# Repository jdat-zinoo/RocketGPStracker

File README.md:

# RocketGPStracker

Atmega328P (arduino based) tiny GPS tracker for model rockets.

Additional package:
https://github.com/SpenceKonde/ATTinyCore
JSon board URL: http://drazzy.com/package_drazzy.com_index.json

TinyWireM lib:
https://github.com/SpenceKonde/TinyWireM

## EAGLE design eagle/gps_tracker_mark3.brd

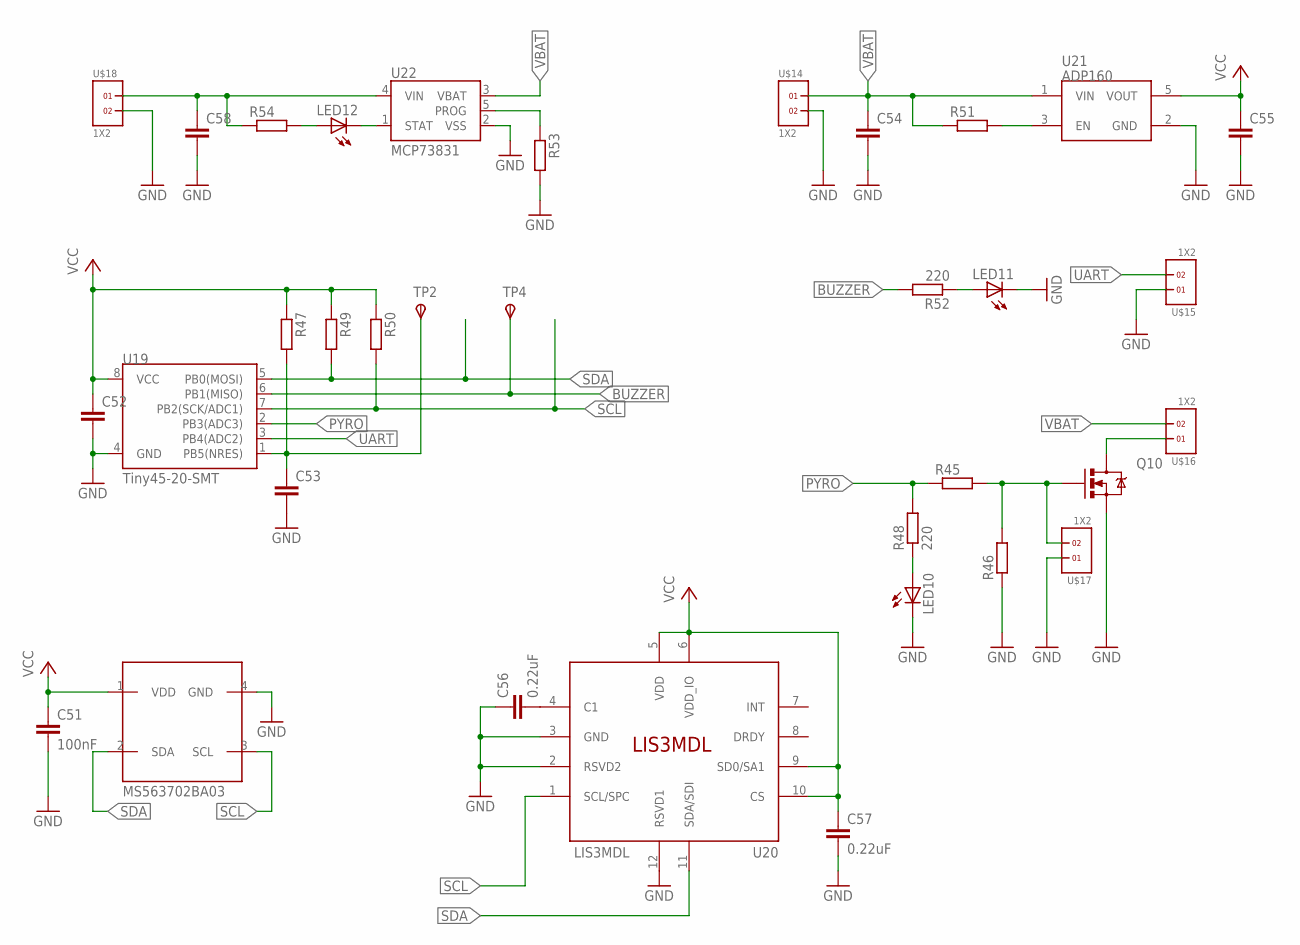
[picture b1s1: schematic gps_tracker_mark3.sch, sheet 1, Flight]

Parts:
C51: 100nF; C0603
C52: C-EUC1206; C1206
C53, C54, C55, C58: C-EUC0603; C0603
C56: 0.22uF; C0603K
C57: 0.22uF; C0603
IC2: MS563702BA03; MS5637
LED10, LED11: LEDCHIPLED_0805; CHIPLED_0805
LED12: LEDCHIPLED_0603; CHIPLED_0603
Q10: MOSFET-NCHANNELBSS123LT1G; SOT23-3
R45, R46, R47, R49, R50, R51, R53, R54: R-EU_R0603; R0603
R48, R52: 220; R0603
TP2, TP4: TPSB1,27; B1,27
U19: Tiny45-20-SMT; SO08-EIAJ
U20: LIS3MDL; VFLGA-12
U21: ADP160; SOT23-5; FARNELL 2510377
U22: MCP73831; SOT23-5; FARNELL 1834892
U$14, U$15, U$16, U$17, U$18: 1X2

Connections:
BUZZER: R52.2, TP4.TP, U19.6 (PB1(MISO))
GND: C51.2, C52.2, C53.2, C54.2, C55.2, C56.1, C57.2, C58.2, IC2.4 (GND), LED10.C, LED11.C, Q10.2 (S), R46.1, R53.2, U19.4 (GND), U20.2 (RSVD2), U20.3 (GND), U20.12 (RSVD1), U21.2 (GND), U22.2 (VSS), U$14.2, U$15.1, U$17.1, U$18.2
unnamed: C53.1, R47.2, TP2.TP, U19.1 (PB5(NRES))
unnamed: Q10.1 (G), R45.2, R46.2, U$17.2
unnamed: LED10.A, R48.1
unnamed: C56.2, U20.4 (C1)
unnamed: R51.2, U21.3 (EN)
unnamed: LED11.A, R52.1
unnamed: Q10.3 (D), U$16.1
unnamed: R53.1, U22.5 (PROG)
unnamed: LED12.C, U22.1 (STAT)
unnamed: LED12.A, R54.2
unnamed: C58.1, R54.1, U22.4 (VIN), U$18.1
PYRO: R45.1, R48.2, U19.2 (PB3(ADC3))
SCL: IC2.3 (SCL), R50.2, U19.7 (PB2(SCK/ADC1)), U20.1 (SCL/SPC)
SDA: IC2.2 (SDA), R49.2, U19.5 (PB0(MOSI)), U20.11 (SDA/SDI)
UART: U19.3 (PB4(ADC2)), U$15.2
VBAT: C54.1, R51.1, U21.1 (VIN), U22.3 (VBAT), U$14.1, U$16.2
VCC: C51.1, C52.1, C55.1, C57.1, IC2.1 (VDD), R47.1, R49.1, R50.1, U19.8 (VCC), U20.5 (VDD), U20.6 (VDD_IO), U20.9 (SD0/SA1), U20.10 (CS), U21.5 (VOUT)

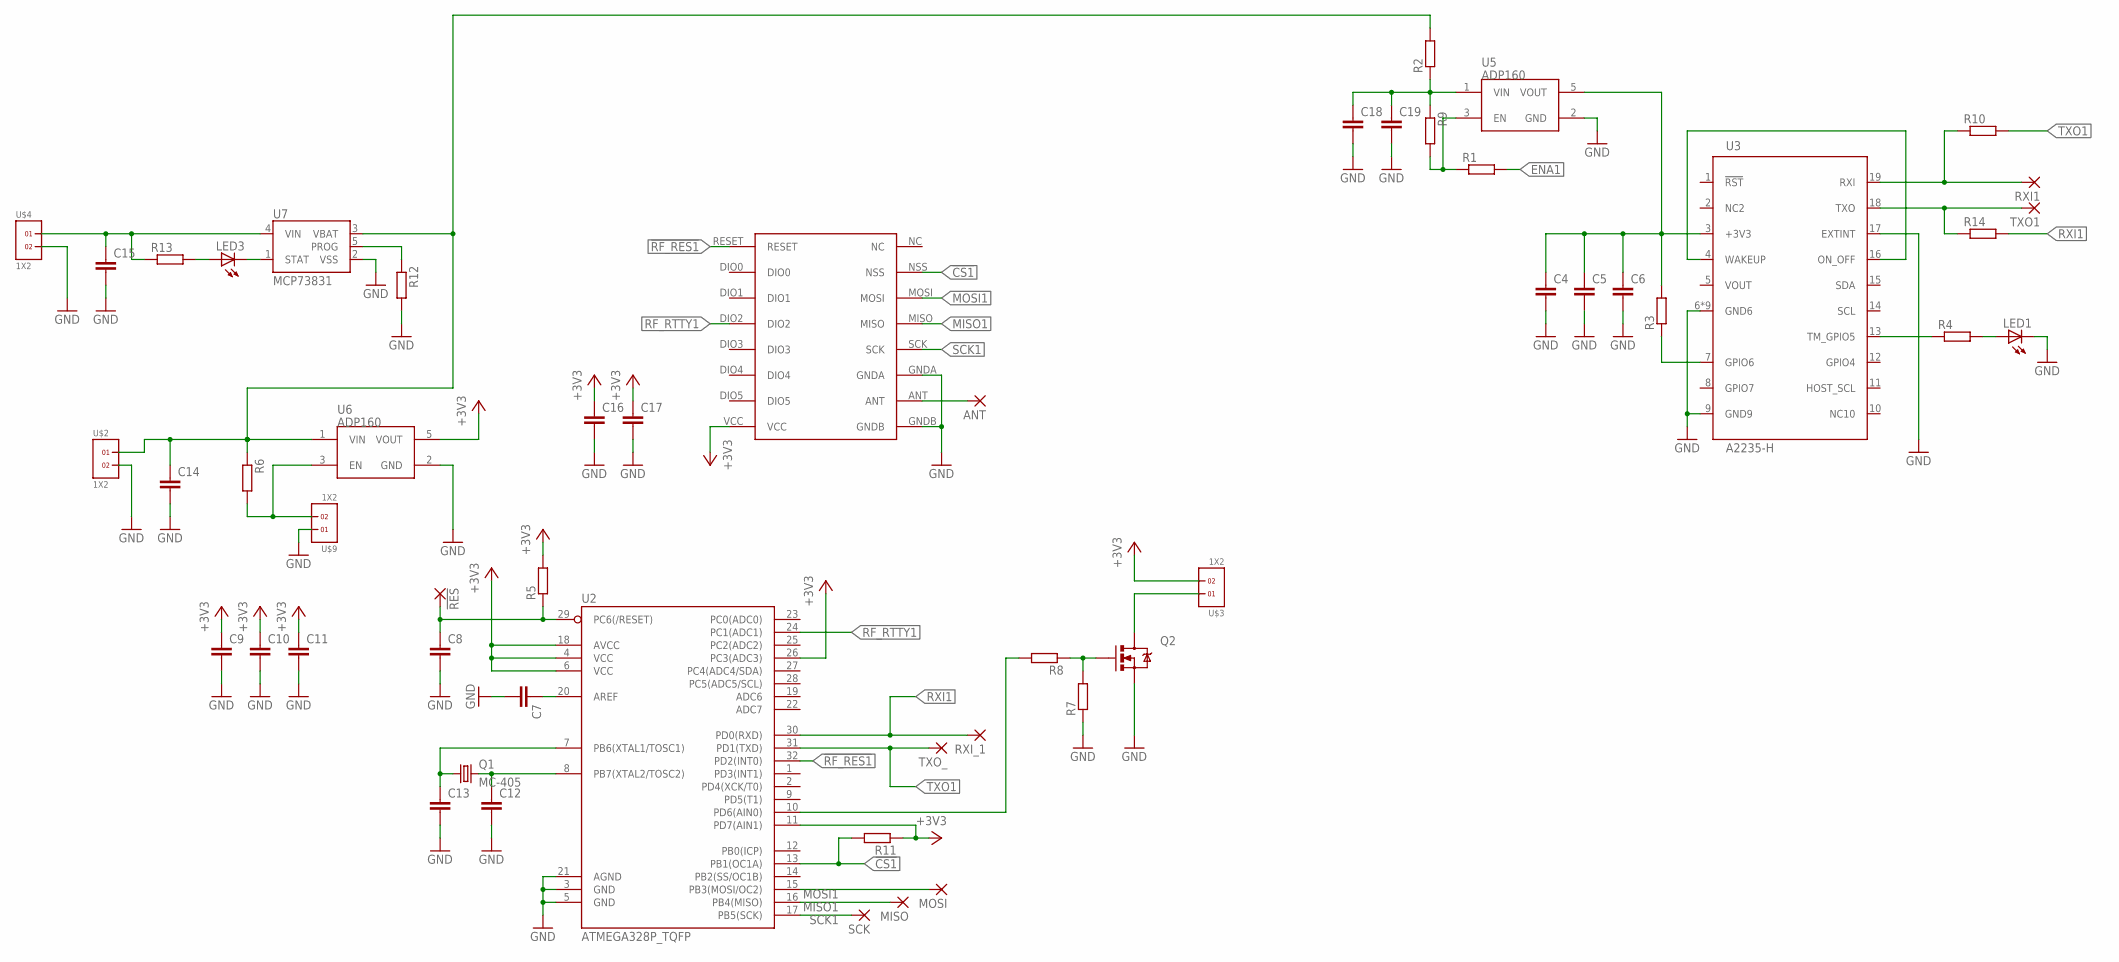
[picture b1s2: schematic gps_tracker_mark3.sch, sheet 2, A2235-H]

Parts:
!RES: SMD2; SMD1,27-2,54
ANT: SMD2; SMD1,27-2,54
C4, C5, C6, C7, C8, C9, C10, C11, C12, C13, C14, C15, C16, C17, C18, C19: C-EUC0603; C0603
LED1, LED3: LEDCHIPLED_0603; CHIPLED_0603
MISO: SMD2; SMD1,27-2,54
MOSI: SMD2; SMD1,27-2,54
Q1: MC-405; FARNELL 2508596
Q2: MOSFET-NCHANNELAO3404A; SOT23-3
R1, R2, R3, R4, R5, R6, R7, R8, R9, R10, R11, R12, R13, R14: R-EU_R0603; R0603
RXI1: SMD2; SMD1,27-2,54
RXI_1: SMD2; SMD1,27-2,54
SCK: SMD2; SMD1,27-2,54
TXO1: SMD2; SMD1,27-2,54
TXO_: SMD2; SMD1,27-2,54
U2: ATMEGA328P_TQFP; TQFP32-08
U3: A2235-H
U5, U6: ADP160; SOT23-5; FARNELL 2510377
U7: MCP73831; SOT23-5; FARNELL 1834892
U$1: RFM69HW; RFM
U$2, U$3, U$4, U$9: 1X2

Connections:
!CS1: R11.2, U2.13 (PB1(OC1A)), U$1.NSS
!RF_RES1: U2.32 (PD2(INT0)), U$1.RESET
+3V3_1: C9.1, C10.1, C11.1, C16.1, C17.1, R5.2, R11.1, U2.4 (VCC), U2.6 (VCC), U2.11 (PD7(AIN1)), U2.18 (AVCC), U2.26 (PC3(ADC3)), U6.5 (VOUT), U$1.VCC, U$3.2
+BAT1: C14.1, R2.2, R6.1, U6.1 (VIN), U7.3 (VBAT), U$2.1
ENA1: R1.2, R6.2, U6.3 (EN), U$9.2
GND1: C4.2, C5.2, C6.2, C7.2, C8.2, C9.2, C10.2, C11.2, C12.2, C13.2, C14.2, C15.2, C16.2, C17.2, C18.2, C19.2, LED1.C, Q2.2 (S), R7.1, R12.2, U2.3 (GND), U2.5 (GND), U2.21 (AGND), U3.6 (GND6), U3.9 (GND9), U3.17 (EXTINT), U3.101 (GND6), U3.102 (GND6), U3.103 (GND6), U3.104 (GND6), U3.105 (GND6), U3.106 (GND6), U3.107 (GND6), U3.108 (GND6), U5.2 (GND), U6.2 (GND), U7.2 (VSS), U$1.GNDA, U$1.GNDB, U$2.2, U$4.2, U$9.1
MISO1: MISO.1, U2.16 (PB4(MISO)), U$1.MISO
MOSI1: MOSI.1, U2.15 (PB3(MOSI/OC2)), U$1.MOSI
unnamed: R1.1, R9.2, U5.3 (EN)
unnamed: C18.1, C19.1, R2.1, R9.1, U5.1 (VIN)
unnamed: R3.1, U3.7 (GPIO6)
unnamed: LED1.A, R4.2
unnamed: R4.1, U3.13 (TM_GPIO5)
unnamed: U3.4 (WAKEUP), U3.16 (ON_OFF)
unnamed: R12.1, U7.5 (PROG)
unnamed: C7.1, U2.20 (AREF)
unnamed: !RES.1, C8.1, R5.1, U2.29 (PC6(/RESET))
unnamed: ANT.1, U$1.ANT
unnamed: C12.1, Q1.2, U2.8 (PB7(XTAL2/TOSC2))
unnamed: C13.1, Q1.1, U2.7 (PB6(XTAL1/TOSC1))
unnamed: LED3.C, U7.1 (STAT)
unnamed: Q2.1 (G), R7.2, R8.1
unnamed: R8.2, U2.10 (PD6(AIN0))
unnamed: Q2.3 (D), U$3.1
unnamed: LED3.A, R13.2
unnamed: C15.1, R13.1, U7.4 (VIN), U$4.1
unnamed: C4.1, C5.1, C6.1, R3.2, U3.3 (+3V3), U5.5 (VOUT)
RF_RTTY1: U2.24 (PC1(ADC1)), U$1.DIO2
RXI1: R14.2, RXI_1.1, U2.30 (PD0(RXD))
RXI_G1: R10.1, RXI1.1, U3.19 (RXI)
SCK1: SCK.1, U2.17 (PB5(SCK)), U$1.SCK
TXO1: R10.2, TXO_.1, U2.31 (PD1(TXD))
TXO_G1: R14.1, TXO1.1, U3.18 (TXO)
VOUT: U3.5 (VOUT)

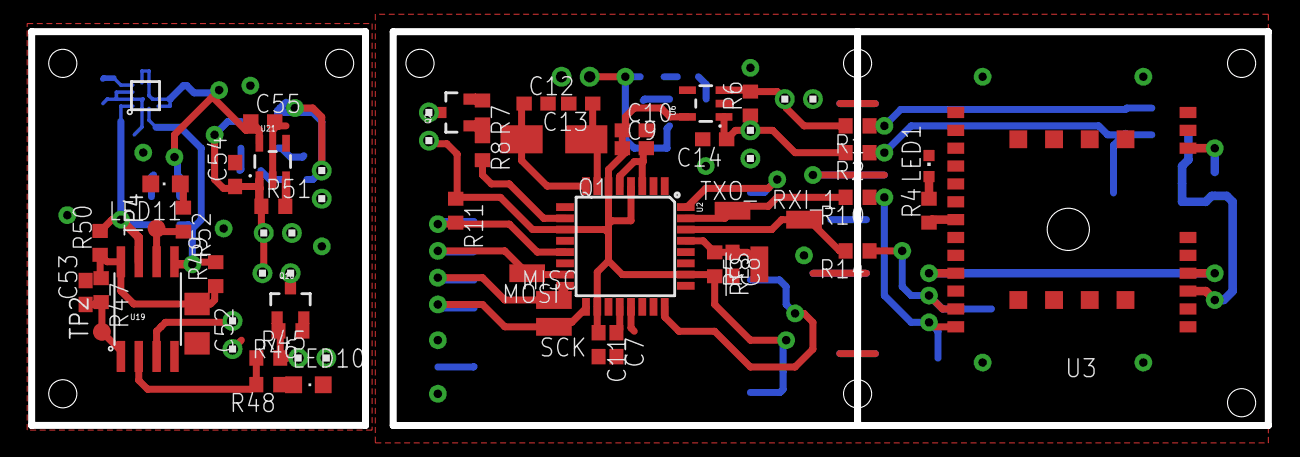
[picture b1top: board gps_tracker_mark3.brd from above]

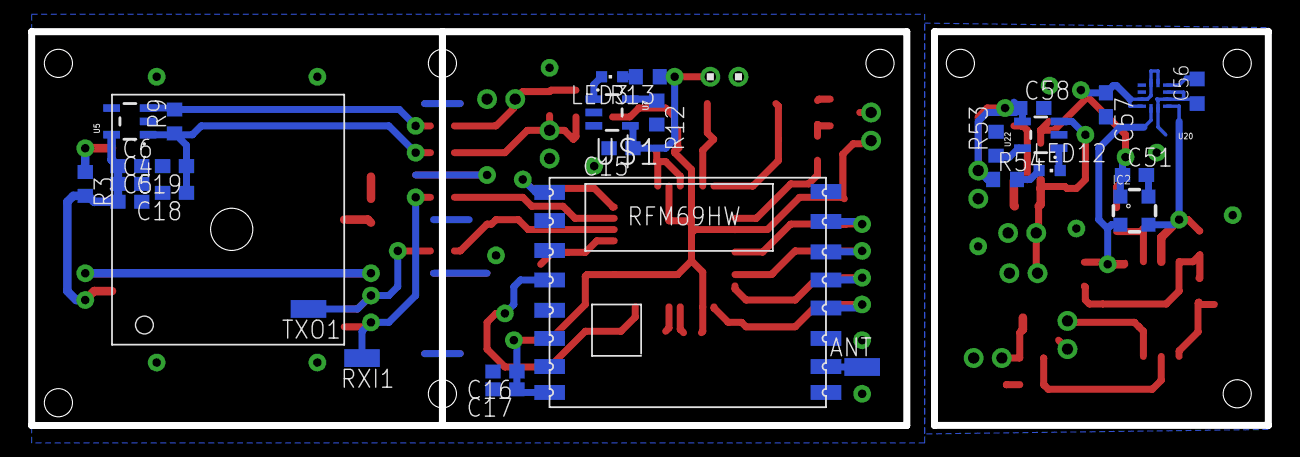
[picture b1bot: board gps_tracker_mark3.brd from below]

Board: 2 copper layers, 87.9 x 28.0 mm, 87 parts (30 on the bottom side), 52 nets.

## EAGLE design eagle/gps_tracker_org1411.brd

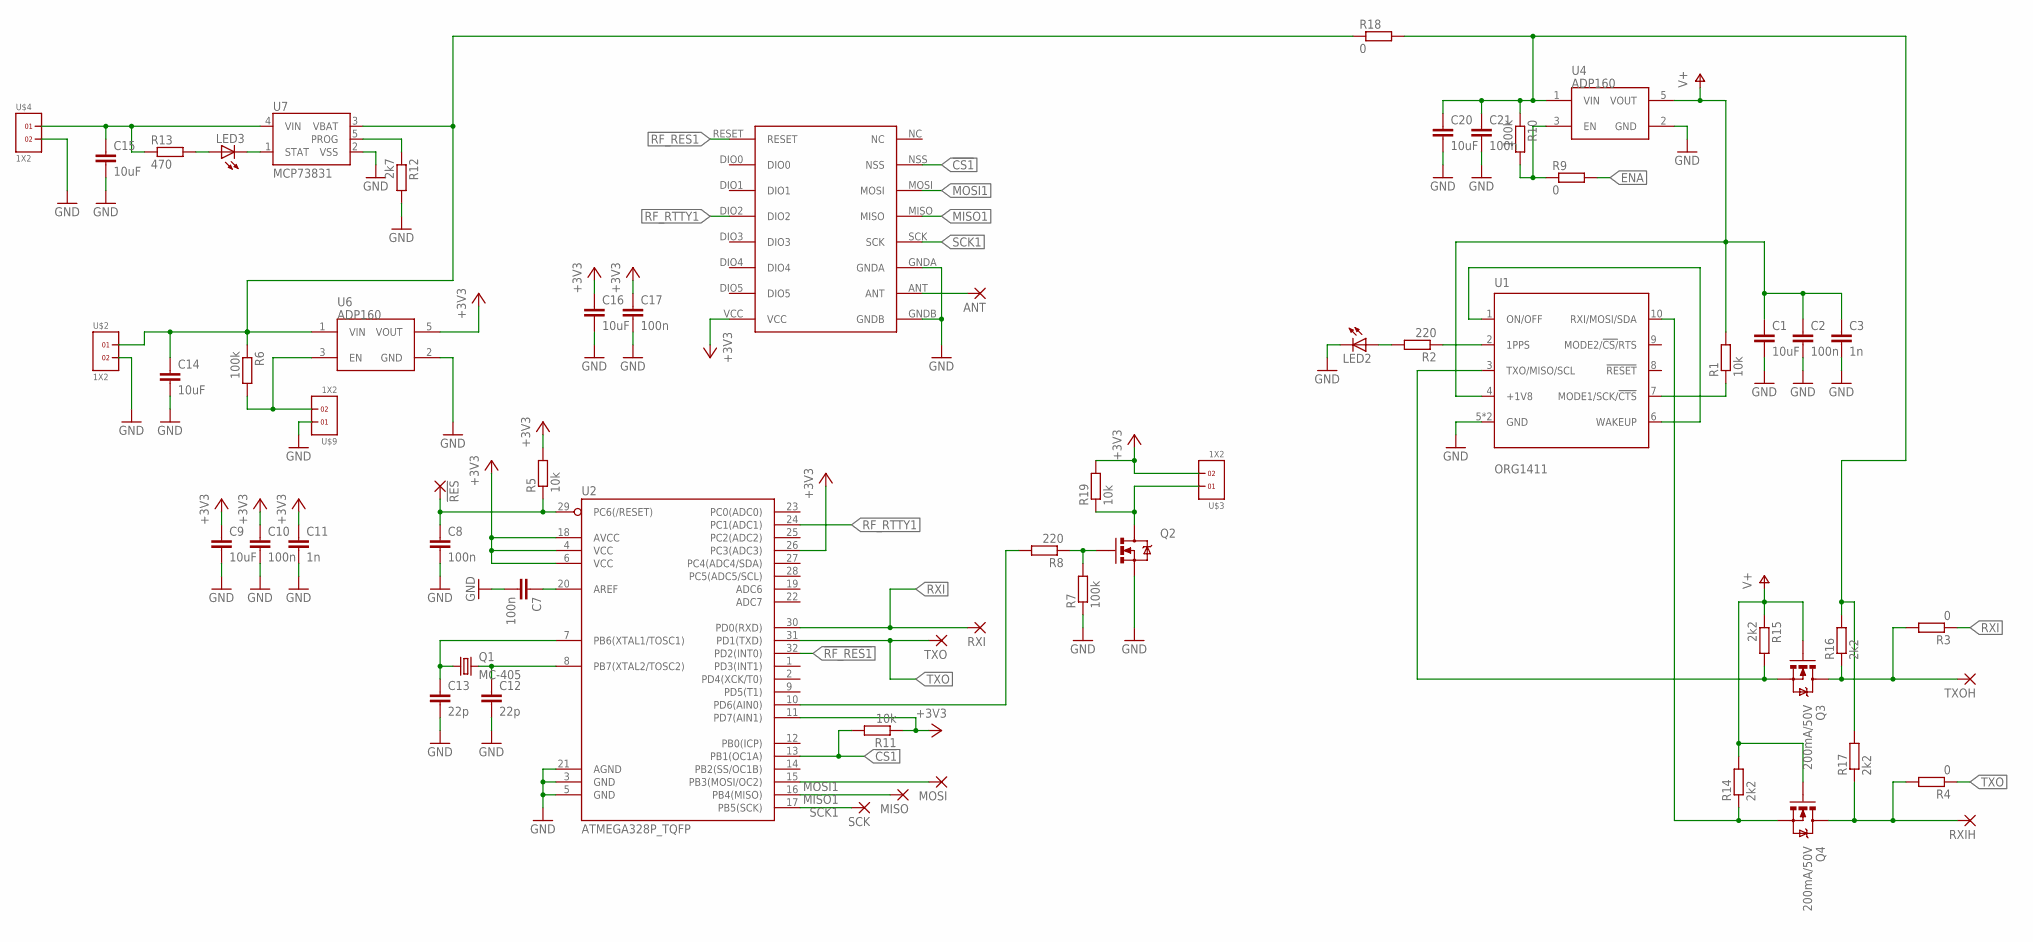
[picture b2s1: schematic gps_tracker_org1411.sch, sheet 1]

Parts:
!RES: SMD2; SMD1,27-2,54
ANT: SMD2; SMD1,27-2,54
C1, C9, C14, C15, C16, C20: 10uF; C0603
C2, C7, C8, C10, C17, C21: 100n; C0603
C3, C11: 1n; C0603
C12, C13: 22p; C0603
LED2, LED3: LEDCHIPLED_0603; CHIPLED_0603
MISO: SMD2; SMD1,27-2,54
MOSI: SMD2; SMD1,27-2,54
Q1: MC-405; FARNELL 2508596
Q2: MOSFET-NCHANNELAO3404A; SOT23-3
Q3, Q4: 200mA/50V; SOT23-3
R1, R5, R11, R19: 10k; R0603
R2, R8: 220; R0603
R3, R4, R9, R18: 0; R0603
R6, R7, R10: 100k; R0603
R12: 2k7; R0603
R13: 470; R0603
R14, R15: 2k2; R0603
R16, R17: 2k2; R1206
RXI: SMD2; SMD1,27-2,54
RXIH: SMD2; SMD1,27-2,54
SCK: SMD2; SMD1,27-2,54
TXO: SMD2; SMD1,27-2,54
TXOH: SMD2; SMD1,27-2,54
U1: ORG1411
U2: ATMEGA328P_TQFP; TQFP32-08
U4: ADP160; SOT23-5; FARNELL 2510505
U6: ADP160; SOT23-5; FARNELL 2510377
U7: MCP73831; SOT23-5; FARNELL 1834892
U$2, U$3, U$4, U$9: 1X2
U$5: RFM69HW; RFM

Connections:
!CS1: R11.2, U2.13 (PB1(OC1A)), U$5.NSS
!RF_RES1: U2.32 (PD2(INT0)), U$5.RESET
+3V3_1: C9.1, C10.1, C11.1, C16.1, C17.1, R5.2, R11.1, R19.2, U2.4 (VCC), U2.6 (VCC), U2.11 (PD7(AIN1)), U2.18 (AVCC), U2.26 (PC3(ADC3)), U6.5 (VOUT), U$3.2, U$5.VCC
+BAT: C14.1, R6.1, R18.1, U6.1 (VIN), U7.3 (VBAT), U$2.1
ENA: R6.2, R9.2, U6.3 (EN), U$9.2
GND: C1.2, C2.2, C3.2, C7.2, C8.2, C9.2, C10.2, C11.2, C12.2, C13.2, C14.2, C15.2, C16.2, C17.2, C20.2, C21.2, LED2.C, Q2.2 (S), R7.1, R12.2, U1.5 (GND), U1.11 (GND), U2.3 (GND), U2.5 (GND), U2.21 (AGND), U4.2 (GND), U6.2 (GND), U7.2 (VSS), U$2.2, U$4.2, U$5.GNDA, U$5.GNDB, U$9.1
MISO1: MISO.1, U2.16 (PB4(MISO)), U$5.MISO
MOSI1: MOSI.1, U2.15 (PB3(MOSI/OC2)), U$5.MOSI
N1: R9.1, R10.2, U4.3 (EN)
unnamed: U1.1 (ON/OFF), U1.6 (WAKEUP)
unnamed: R1.1, U1.7 (MODE1/SCK/!CTS)
unnamed: R2.1, U1.2 (1PPS)
unnamed: LED2.A, R2.2
unnamed: Q3.2 (S), R15.2, U1.3 (TXO/MISO/SCL)
unnamed: C20.1, C21.1, R10.1, R16.2, R17.2, R18.2, U4.1 (VIN)
unnamed: R12.1, U7.5 (PROG)
unnamed: C7.1, U2.20 (AREF)
unnamed: !RES.1, C8.1, R5.1, U2.29 (PC6(/RESET))
unnamed: ANT.1, U$5.ANT
unnamed: C12.1, Q1.2, U2.8 (PB7(XTAL2/TOSC2))
unnamed: C13.1, Q1.1, U2.7 (PB6(XTAL1/TOSC1))
unnamed: LED3.C, U7.1 (STAT)
unnamed: Q2.1 (G), R7.2, R8.1
unnamed: R8.2, U2.10 (PD6(AIN0))
unnamed: Q2.3 (D), R19.1, U$3.1
unnamed: LED3.A, R13.2
unnamed: C15.1, R13.1, U7.4 (VIN), U$4.1
unnamed: Q3.3 (D), R3.2, R16.1, TXOH.1
unnamed: Q4.3 (D), R4.2, R17.1, RXIH.1
unnamed: Q4.2 (S), R14.1, U1.10 (RXI/MOSI/SDA)
RF_RTTY1: U2.24 (PC1(ADC1)), U$5.DIO2
RXI: R3.1, RXI.1, U2.30 (PD0(RXD))
SCK1: SCK.1, U2.17 (PB5(SCK)), U$5.SCK
TXO: R4.1, TXO.1, U2.31 (PD1(TXD))
V+: C1.1, C2.1, C3.1, Q3.1 (G), Q4.1 (G), R1.2, R14.2, R15.1, U1.4 (+1V8), U4.5 (VOUT)

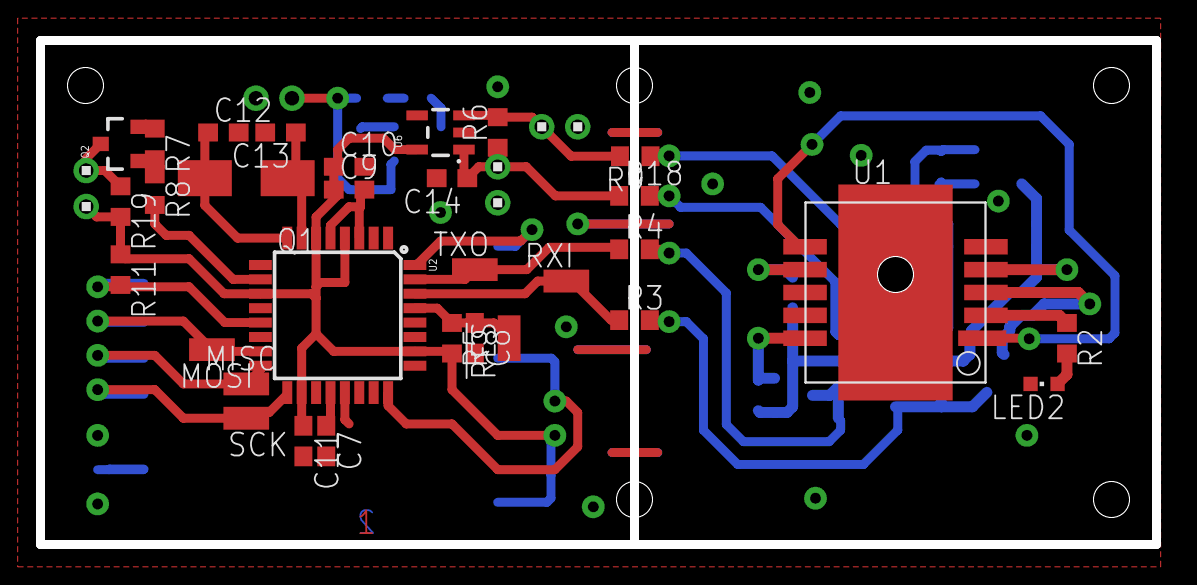
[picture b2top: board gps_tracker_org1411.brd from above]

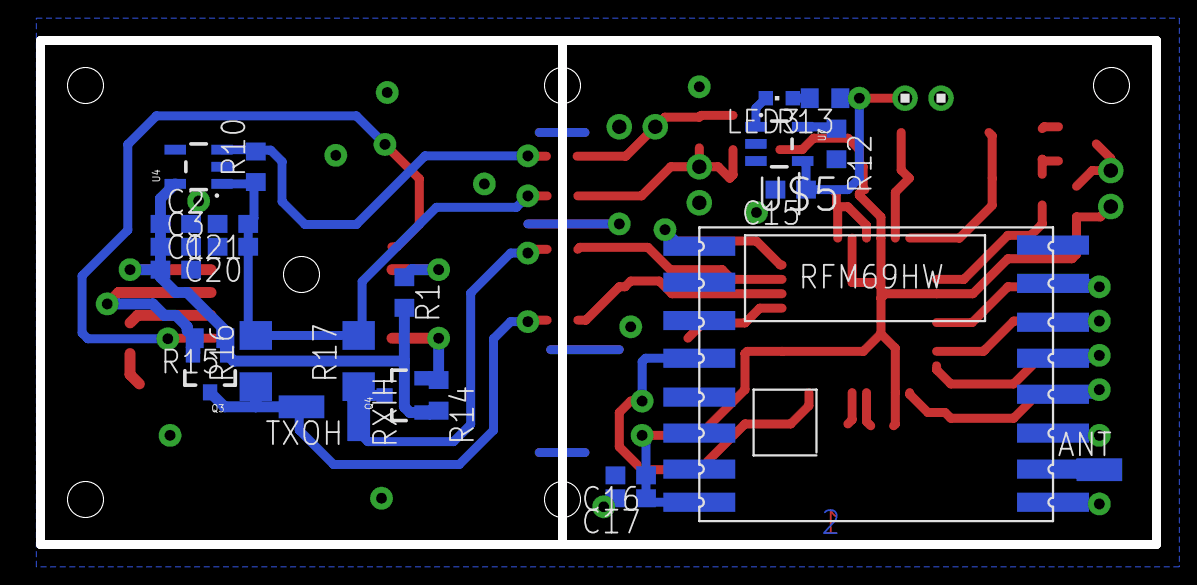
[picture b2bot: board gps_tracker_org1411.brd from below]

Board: 2 copper layers, 62.0 x 28.0 mm, 60 parts (26 on the bottom side), 35 nets.

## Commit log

2017-03-08 Create eagle
2017-07-29 tracker code update
    tracker code update to HW version 2.
    RTTY TX pin now is PORTC 2
2018-02-10 868Mhz version
2018-02-10 Fixed frequency to 868 MHz and shift to 850 Hz

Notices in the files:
parts and their libraries:
SparkFun-DigitalIC: Licensing: Creative Commons ShareAlike 4.0 International - https://creativecommons.org/licenses/by-sa/4.0
freetronics-original: Licensing: CC v3.0 Share-Alike You are welcome to use this library for commercial purposes.
